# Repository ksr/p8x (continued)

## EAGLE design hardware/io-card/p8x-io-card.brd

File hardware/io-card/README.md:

# I/O Card

> **Theory of operation:** [p8x-io-card-theory.md](p8x-io-card-theory.md) — deep walkthrough of inputs/outputs, signal flow, and logic.

All memory-mapped I/O lives here: an 8-switch input port, an 8-LED output port,
**two** RS-232 serial channels via 6850 ACIAs (rev B), and a passive **bus-monitor**
LED display that turns the machine into an Altair-style "watch it think" front panel.

> **Rev B (2026-09-19)** — the routed KiCad board in [`kicad/`](kicad/README.md)
> (not yet fabricated) adds a second 6850 (**U17**, ACIA2 at `$FF08/09`, the
> Kermit / serial-terminal port) on the MAX232's second channel, with its E-gate
> inverter in **U18** (74HCT14). Each channel has its own **DB9** socket and a
> 2×3 jumper block that swaps RX/TX (straight or null-modem). A DS1302 real-time
> clock (**U16**) is provisioned but not fitted (DNP): it is a bit-banged 3-wire
> part on header J3, not memory-mapped. The text below describes the rev A
> circuit, which rev B keeps.

| Address | Port |
|---------|------|
| `$FF00` | Switch input — 8 toggle switches → data bus on read |
| `$FF02` | LED output — 74374 latch → 8 LEDs on write |
| `$FF04` | 6850 ACIA control/status |
| `$FF05` | 6850 ACIA data (RS-232 TX/RX) |
| `$FF08` | ACIA2 control/status (rev B) |
| `$FF09` | ACIA2 data (rev B) |

> This README describes the circuit as actually built in
> [`generators/gen_eagle.py`](../../generators/gen_eagle.py). See
> [p8x-system-design.md §7](../../docs/p8x-system-design.md) for the overview and
> [p8x-bus-definition.md](../backplane/p8x-bus-definition.md) for bus pins.

## Chip inventory

| Ref | Device | Role |
|-----|--------|------|
| U1 | 7430 | 8-input NAND — I/O page ($FFxx) detector |
| U2 | 74138 | Port decoder (A1–A3 → up to 8 port selects) |
| U3 | 74138 | DOE decoder (read enable) |
| U4 | 74138 | DLD decoder (write strobe) |
| U5 | 74HCT32 | OR glue (read/write strobe gating) |
| U6 | 74HCT08 | AND glue (ACIA enable) |
| U7 | 74161 | Baud-rate divider |
| U8 | MAX232 | RS-232 level shifter (the one non-TTL part) |
| U9 | 74244 | Switch-input buffer |
| U10 | 74374 | LED output latch |
| U11–U13 | 74244 | Bus monitors — A0–7, A8–15, D0–7 |
| U14 | 6850 | ACIA (asynchronous serial) |
| U15 | 74HCT00 | NAND glue |
| U16 | DS1302 | Real-time clock, DNP (rev B; 3-wire on J3, not memory-mapped) |
| U17 | 6850 | ACIA2 at `$FF08/09` (rev B) |
| U18 | 74HCT14 | Inverter — ACIA2 enable gate (rev B) |
| X2 | 2.4576 MHz osc | Baud clock source |

## How it works

### Port decoding
U1 (7430) detects the `$FFxx` page exactly as on the memory card. Within the page,
U2 (74138) decodes the low address lines into individual port selects (`-P0`, `-P1`,
`-P2`, …). Read vs write comes from the DOE decoder (U3 → `-RD`) and DLD decoder
(U4 → `-MEMW`), gated in U5/U6 into per-port read/write strobes.

### Switch input ($FF00)
Eight toggle switches with a SIP pull-up network feed a 74244 (U9). On a read of
`$FF00`, U9 is enabled and drives the switch states onto D0–D7.

### LED output ($FF02)
On a write to `$FF02`, the 74374 (U10) latches D0–D7. Its outputs drive an LED bank
through series-resistor networks, so the port value is visible at a glance.

### Serial (6850 ACIA, $FF04–$FF05)
The **6850 ACIA** (U14) handles asynchronous serial. Its enable is the `$FF04/05`
port select gated with the clock (U6/U15) for correct E-clock timing. A **74161**
(U7) divides the dedicated **2.4576 MHz** oscillator (X2) by 16 to make the
TX/RX baud clock. The **MAX232** (U8) — the one concession to non-TTL parts —
converts the ACIA's TTL levels to/from RS-232 ±voltages on the serial header,
using its four external charge-pump capacitors.

### Bus-monitor display (passive)
Three 74244 buffers (U11/U12/U13) permanently sample A0–7, A8–15, and D0–7 and
drive three LED banks. They cost nothing logically — no decode, no bus access —
but combined with the control card's single-step button they let you literally
watch the address and data buses change one microcycle at a time.

## Bus codes this card owns
- **DOE:** 7 = read (the active port drives D0–D7) — shared decode convention with memory
- **DLD:** 7 = write (`MEMW`) — the active port latches D0–D7

## LEDs
PWR (green), IOSEL (yellow — an I/O port is selected), plus the LED output port and
the 24-bit bus-monitor banks.

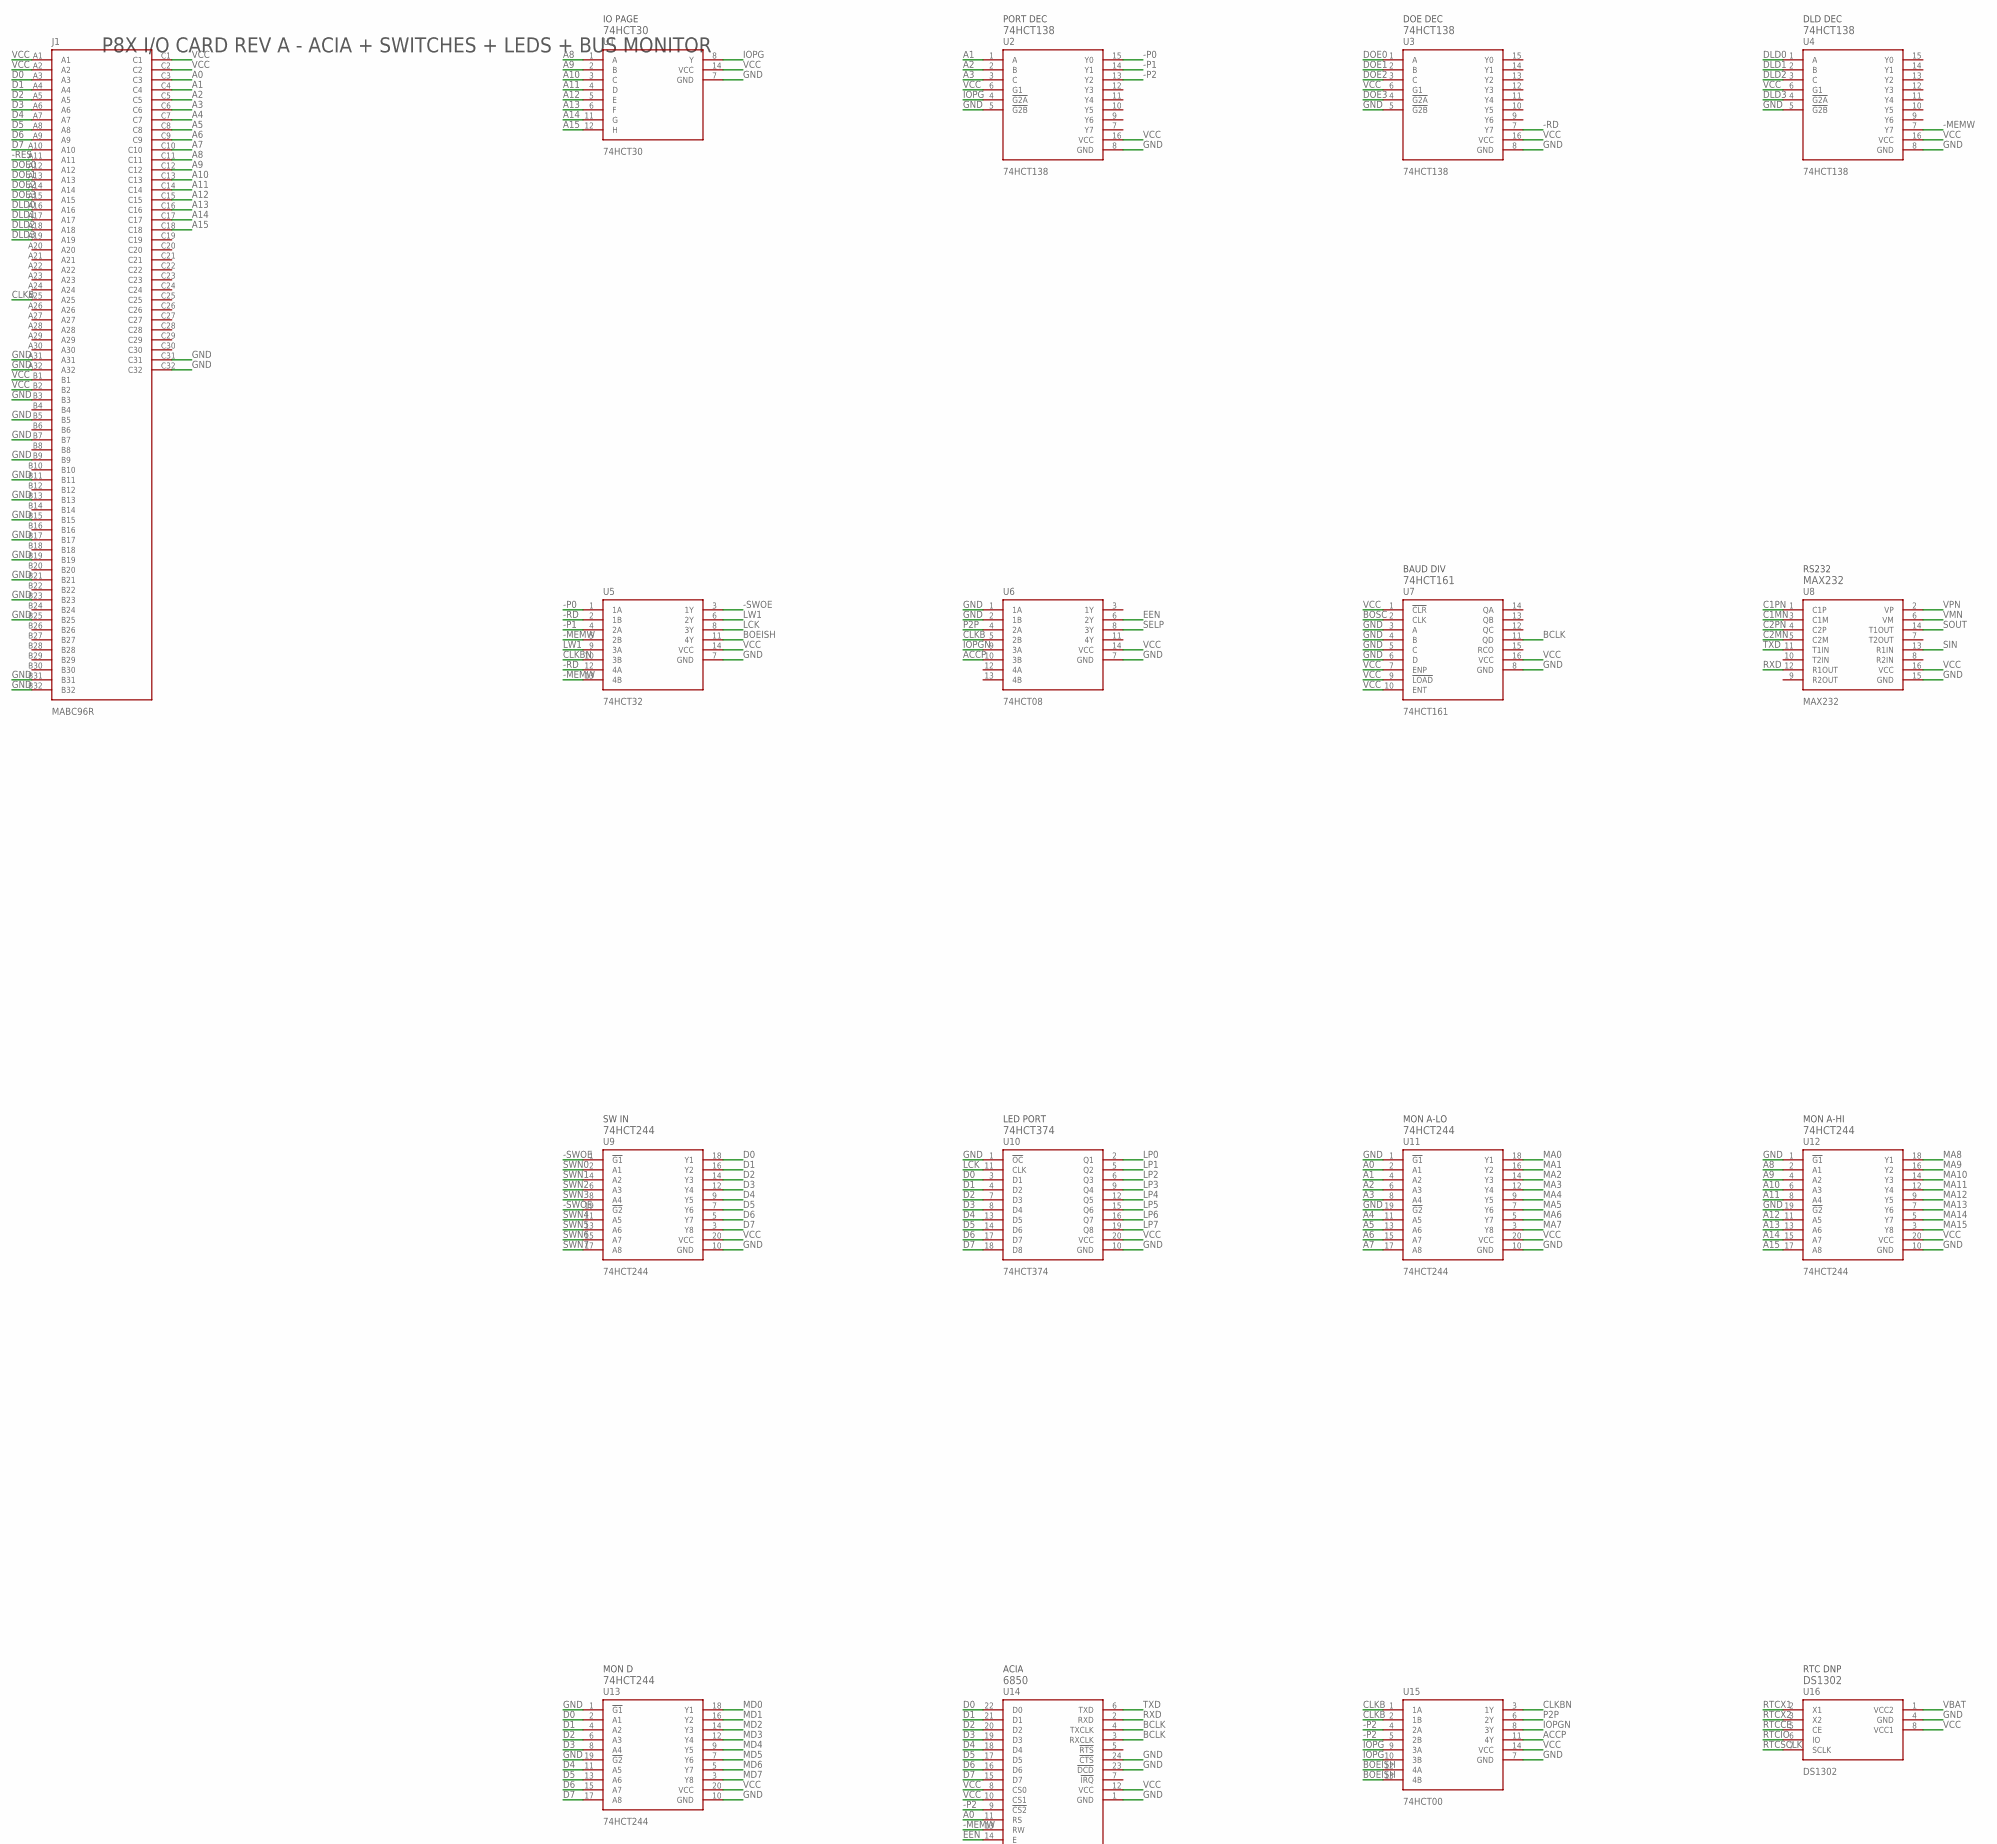
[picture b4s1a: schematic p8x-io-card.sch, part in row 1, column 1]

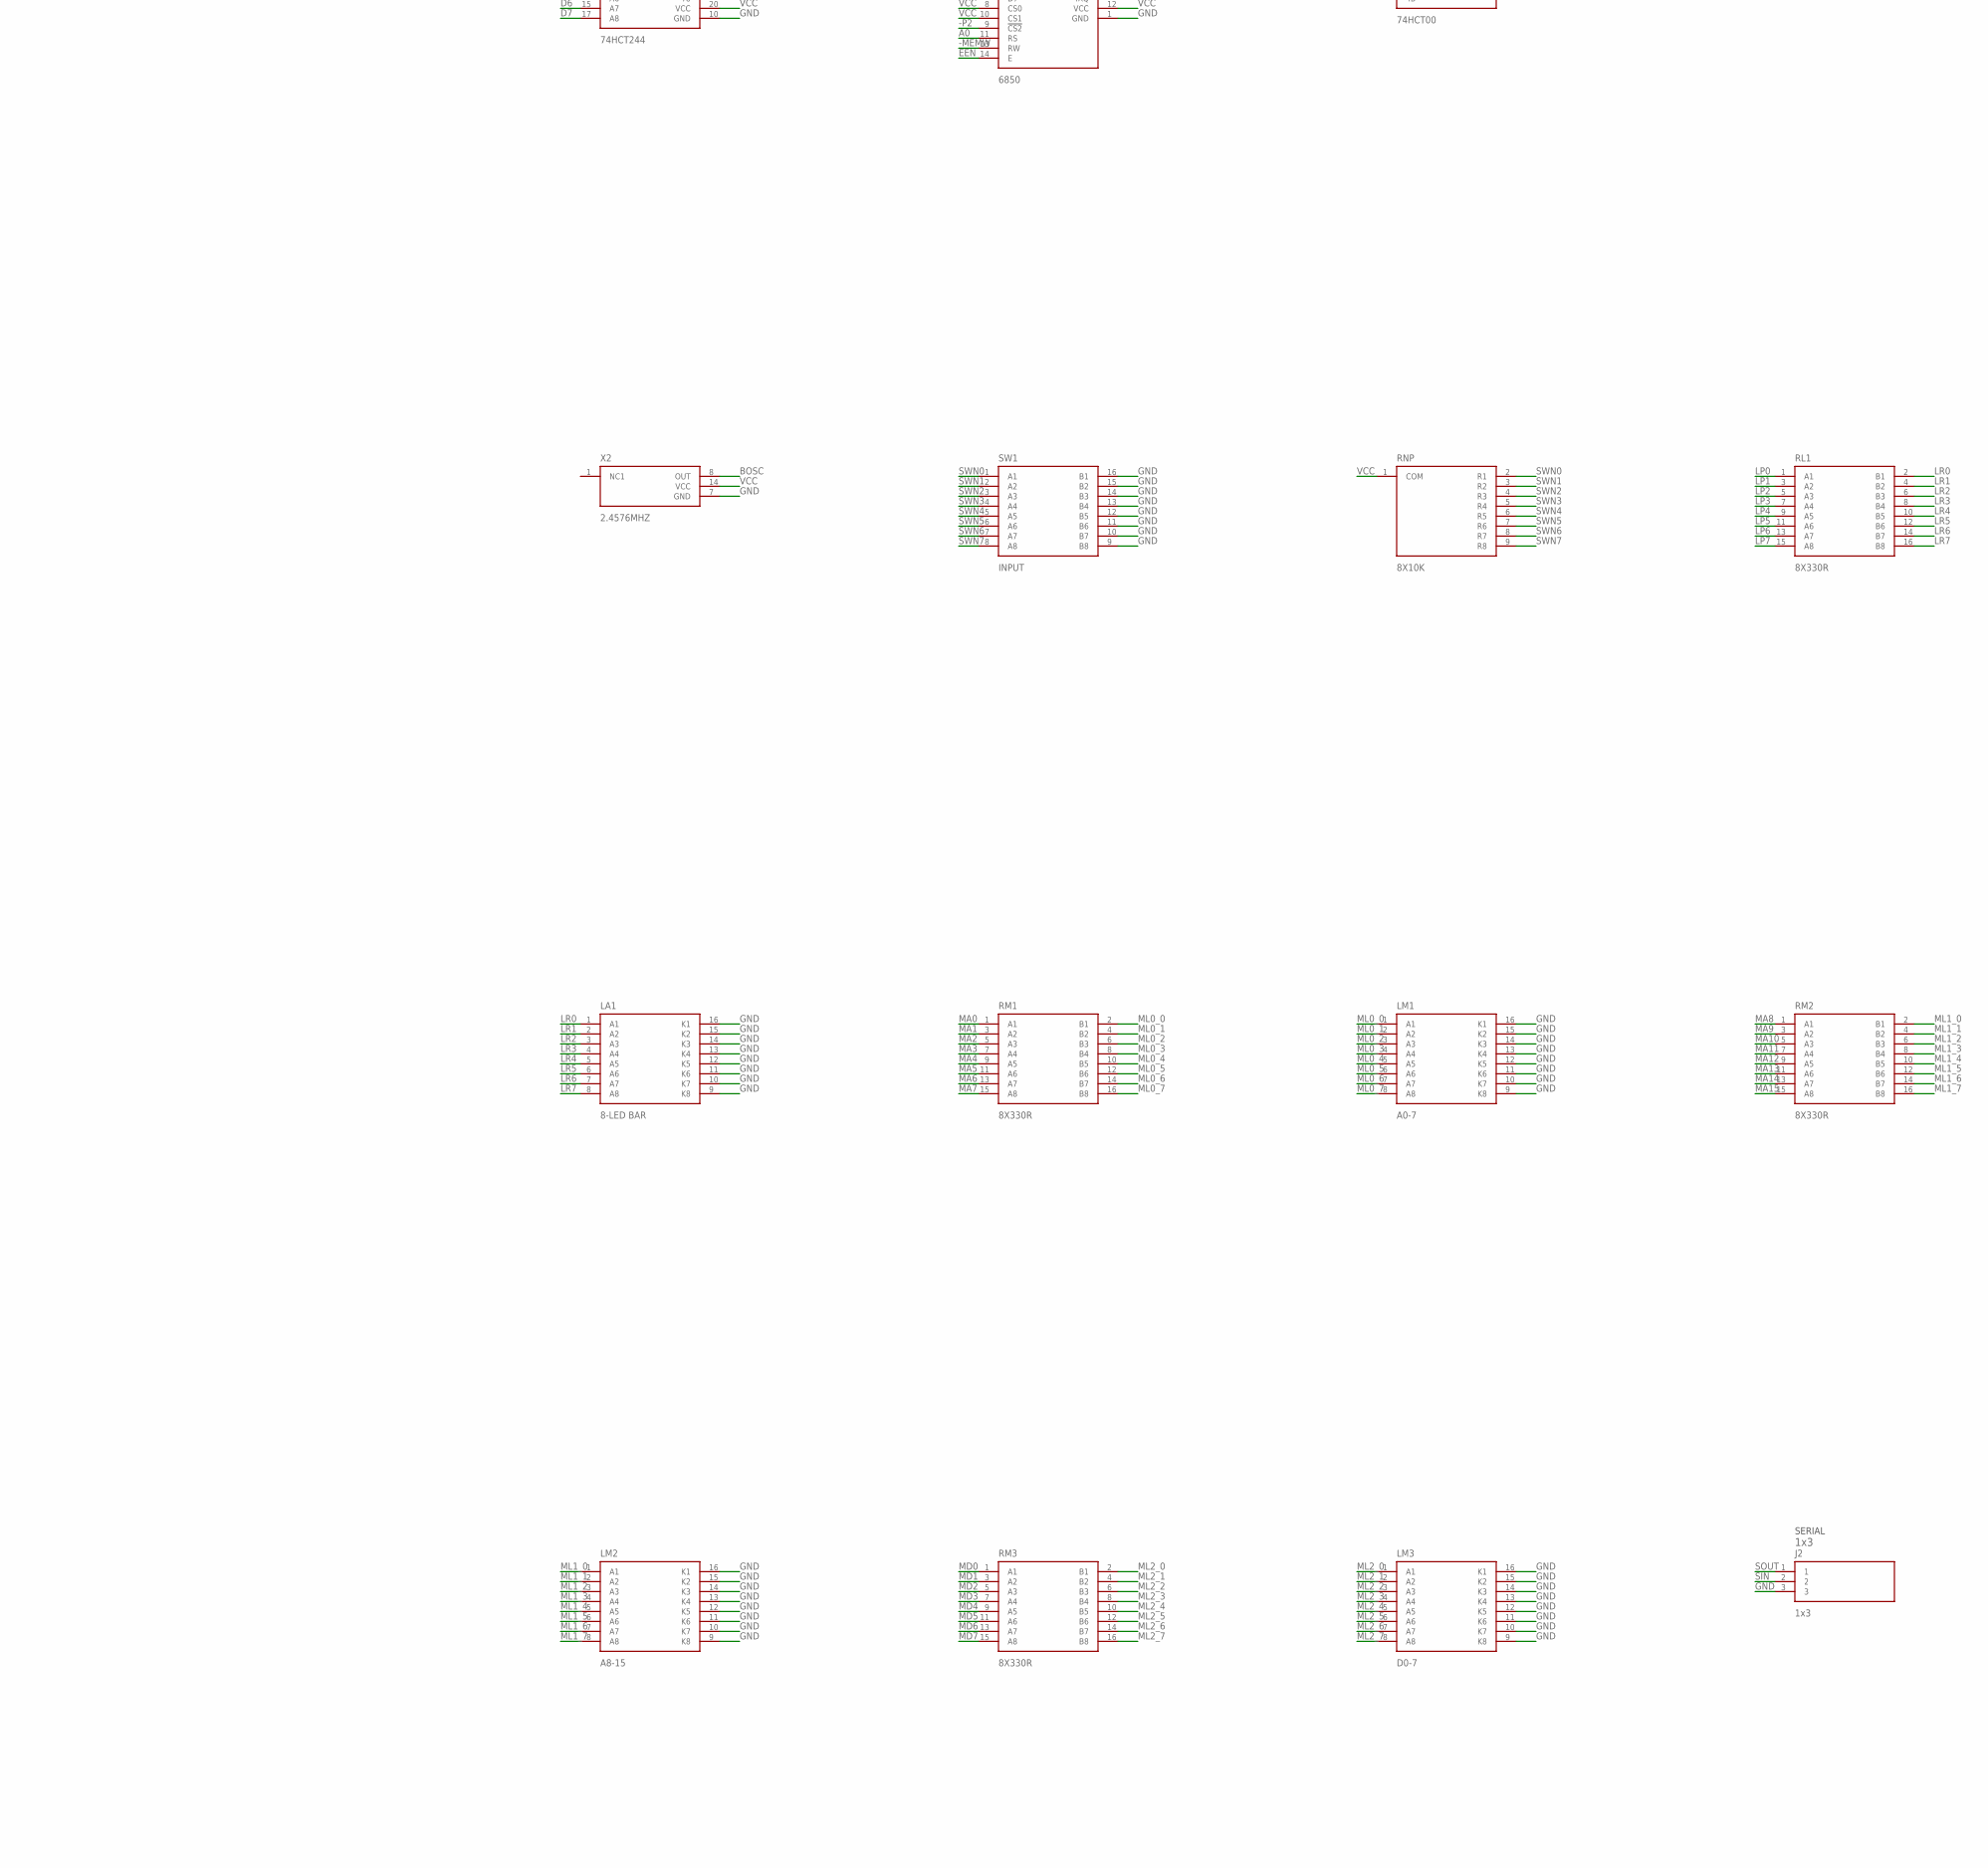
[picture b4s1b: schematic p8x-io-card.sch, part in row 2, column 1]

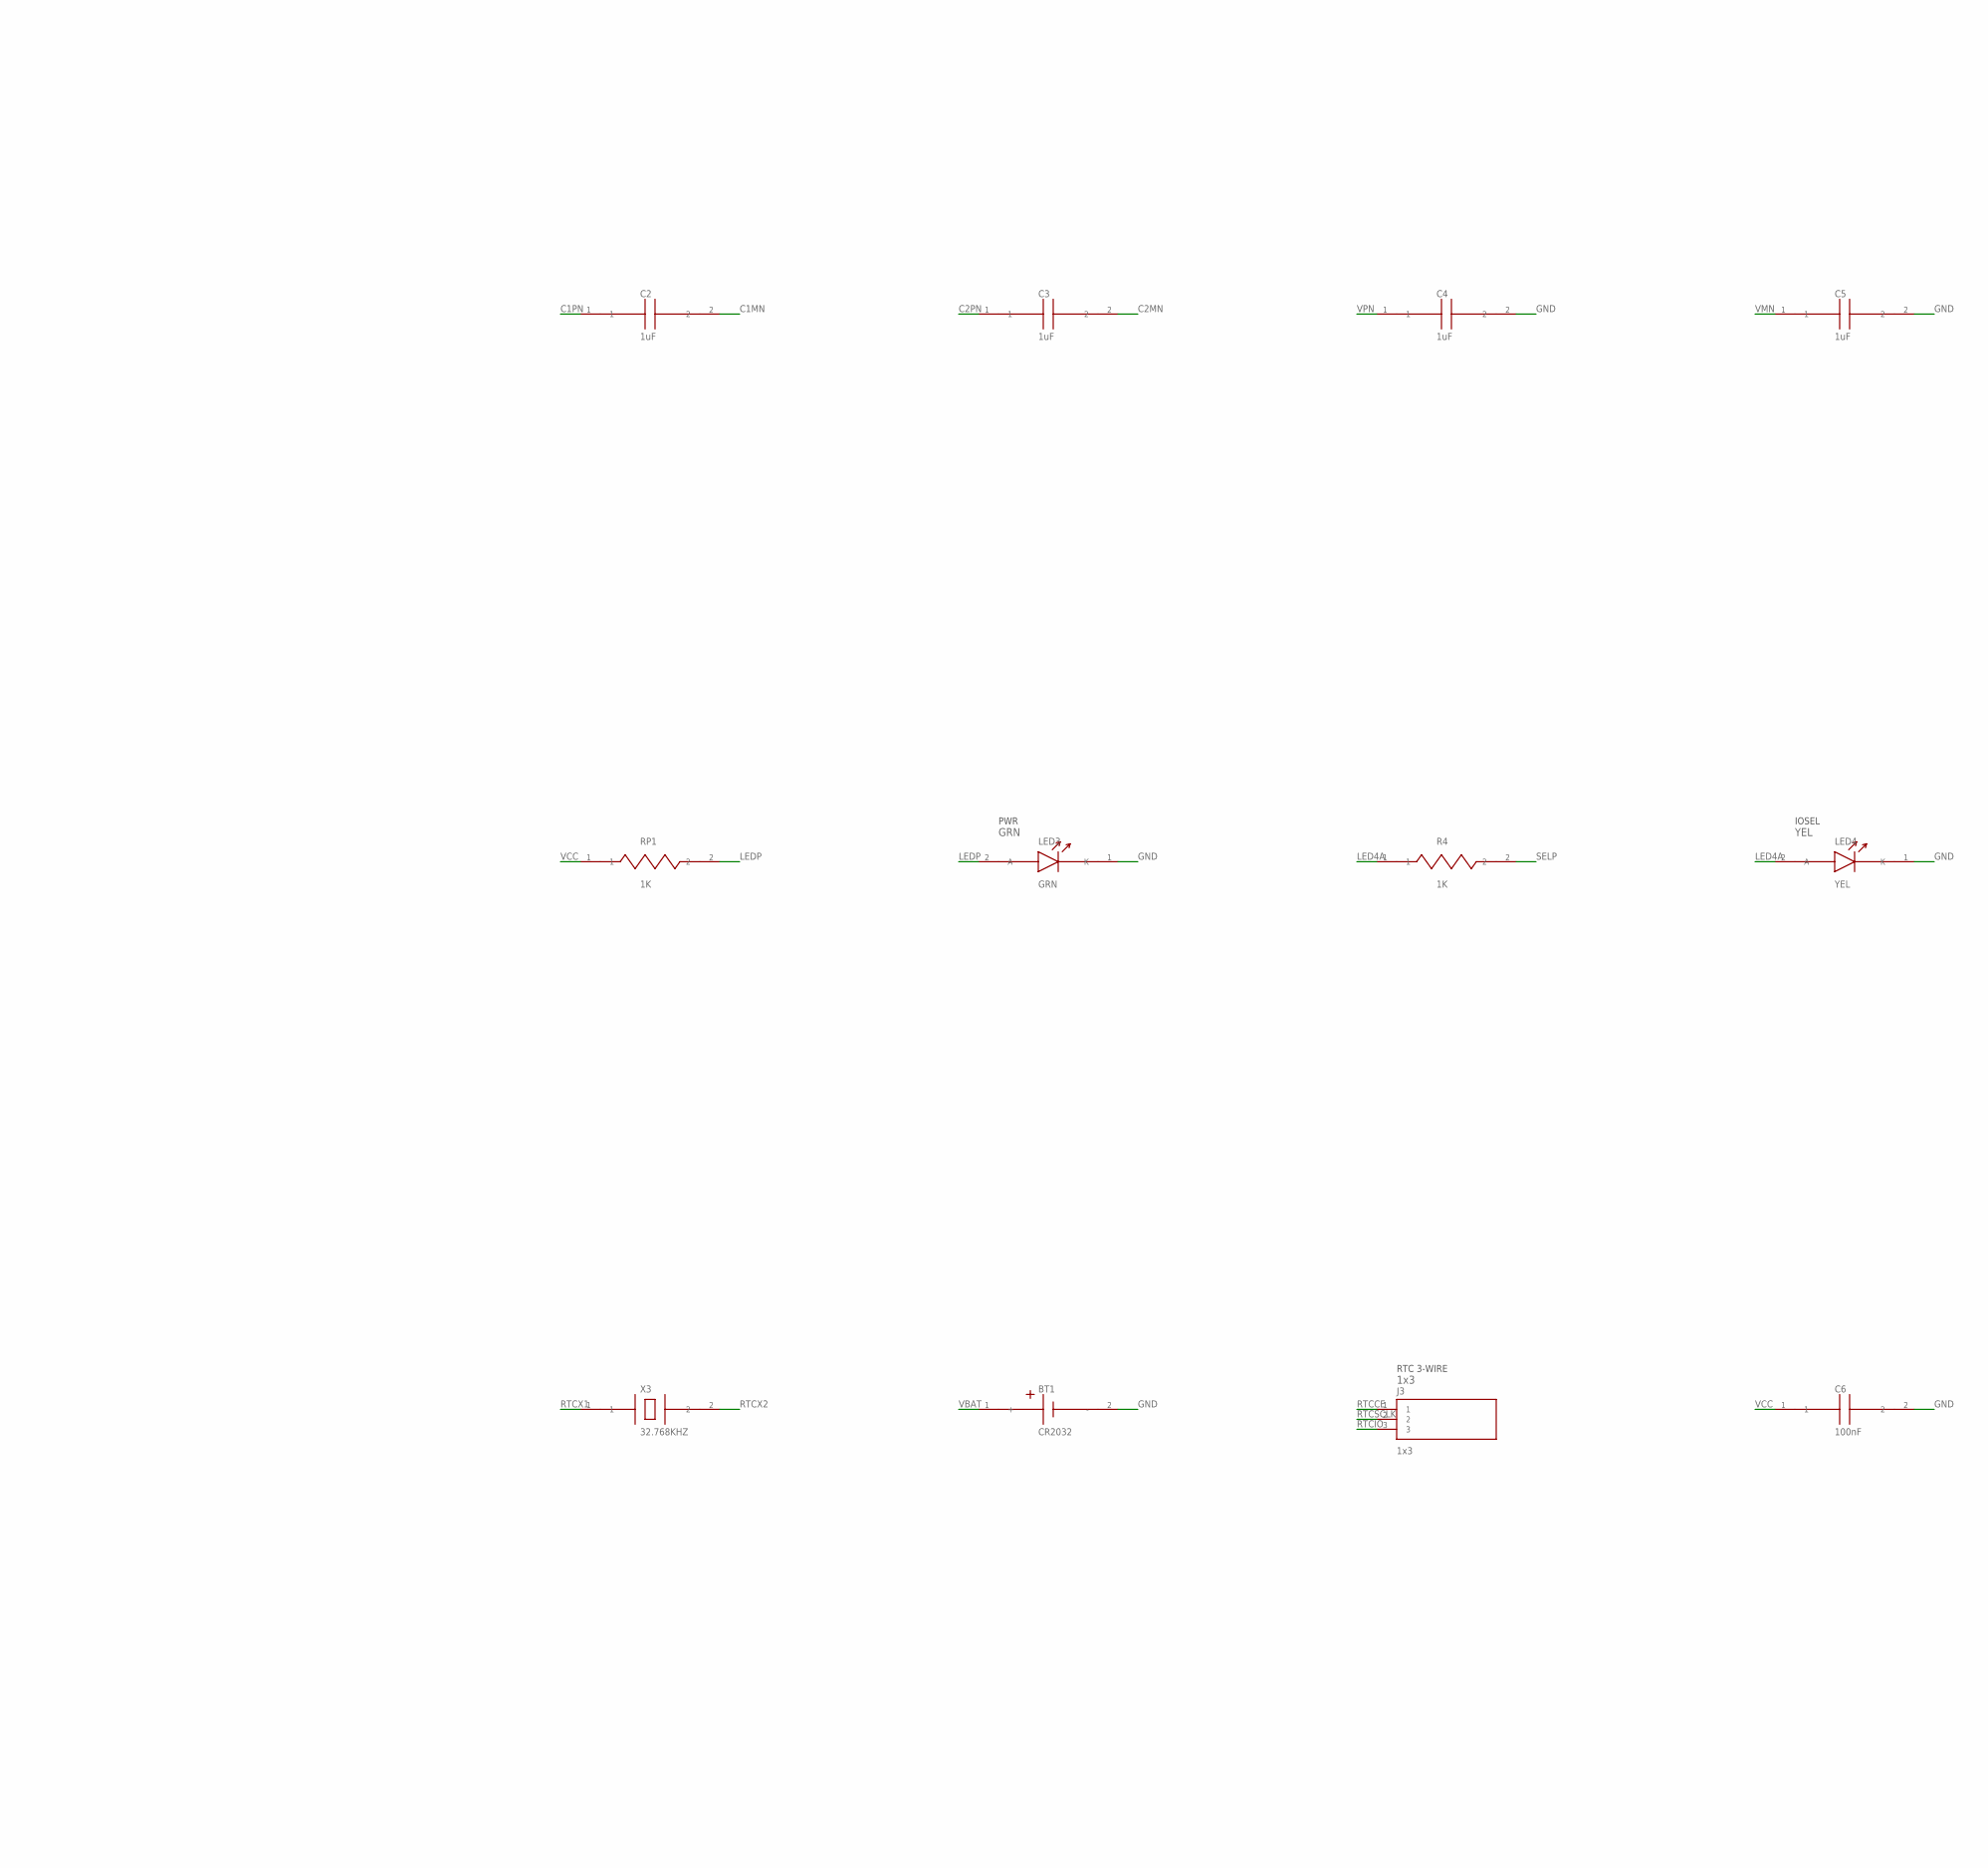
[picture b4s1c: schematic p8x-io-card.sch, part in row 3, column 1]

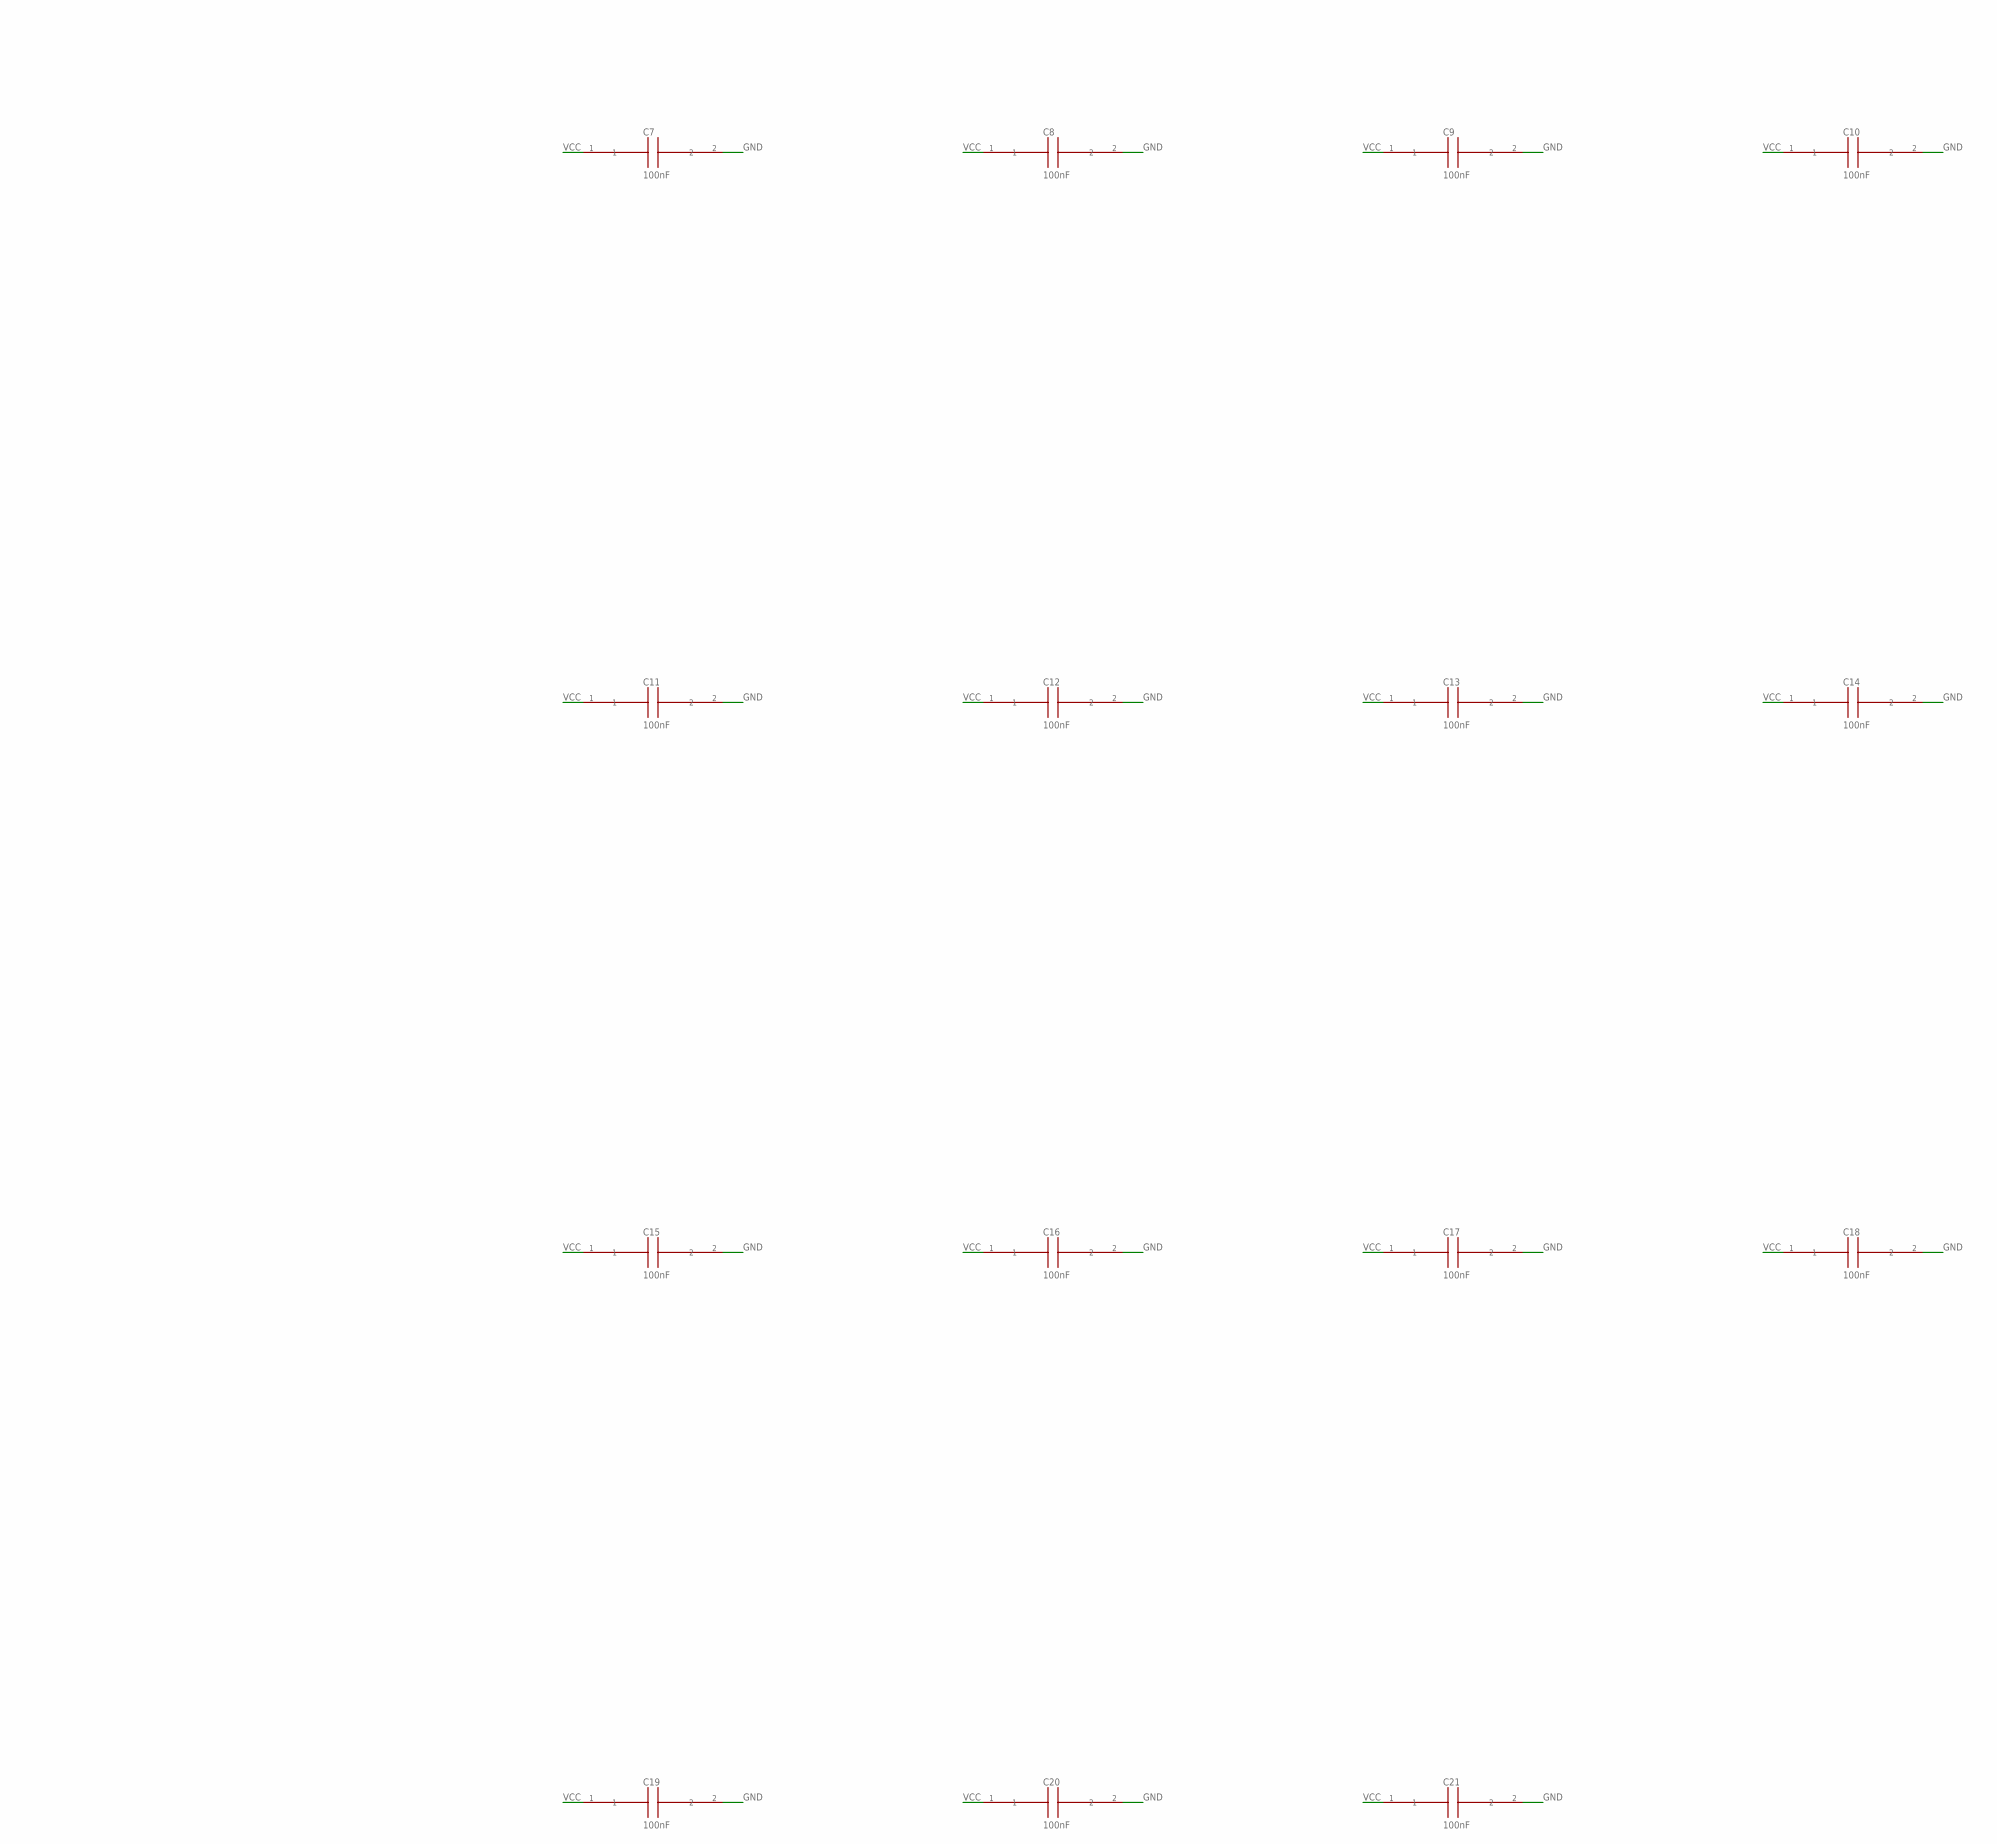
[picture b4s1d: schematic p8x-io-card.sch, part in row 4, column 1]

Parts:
BT1: CR2032; CP_RADIAL
C2, C3, C4, C5: 1uF; C_DISC
C6, C7, C8, C9, C10, C11, C12, C13, C14, C15, C16, C17, C18, C19, C20, C21: 100nF; C_DISC1
J1: MABC96R
J2, J3: 1x3; HDR3
LA1: 8-LED BAR; DIP16
LED3: GRN; LED5
LED4: YEL; LED5
LM1: A0-7; DIP16
LM2: A8-15; DIP16
LM3: D0-7; DIP16
R4: 1K; R_AXIAL
RL1: 8X330R; SIP16
RM1, RM2, RM3: 8X330R; SIP16
RNP: 8X10K; SIP9
RP1: 1K; R_AXIAL
SW1: INPUT; DIP16
U1: 74HCT30; DIP14
U2, U3, U4: 74HCT138; DIP16
U5: 74HCT32; DIP14
U6: 74HCT08; DIP14
U7: 74HCT161; DIP16
U8: MAX232; DIP16
U9, U11, U12, U13: 74HCT244; DIP20
U10: 74HCT374; DIP20
U14: 6850; DIP24W
U15: 74HCT00; DIP14
U16: DS1302; DIP8
X2: 2.4576MHZ; OSC4
X3: 32.768KHZ; C_DISC

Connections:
-MEMW: U4.7 (Y7), U5.5 (2B), U5.13 (4B), U14.13 (RW)
-P0: U2.15 (Y0), U5.1 (1A)
-P1: U2.14 (Y1), U5.4 (2A)
-P2: U2.13 (Y2), U14.9 (!CS2), U15.4 (2A), U15.5 (2B)
-RD: U3.7 (Y7), U5.2 (1B), U5.12 (4A)
-RES: J1.A11
-SWOE: U5.3 (1Y), U9.1 (!G1), U9.19 (!G2)
A0: J1.C3, U11.2 (A1), U14.11 (RS)
A1: J1.C4, U2.1 (A), U11.4 (A2)
A2: J1.C5, U2.2 (B), U11.6 (A3)
A3: J1.C6, U2.3 (C), U11.8 (A4)
A4: J1.C7, U11.11 (A5)
A5: J1.C8, U11.13 (A6)
A6: J1.C9, U11.15 (A7)
A7: J1.C10, U11.17 (A8)
A8: J1.C11, U1.1 (A), U12.2 (A1)
A9: J1.C12, U1.2 (B), U12.4 (A2)
A10: J1.C13, U1.3 (C), U12.6 (A3)
A11: J1.C14, U1.4 (D), U12.8 (A4)
A12: J1.C15, U1.5 (E), U12.11 (A5)
A13: J1.C16, U1.6 (F), U12.13 (A6)
A14: J1.C17, U1.11 (G), U12.15 (A7)
A15: J1.C18, U1.12 (H), U12.17 (A8)
ACCP: U6.10 (3B), U15.11 (4Y)
BCLK: U7.11 (QD), U14.3 (RXCLK), U14.4 (TXCLK)
BOEISH: U5.11 (4Y), U15.12 (4A), U15.13 (4B)
BOSC: U7.2 (CLK), X2.8 (OUT)
C1MN: C2.2, U8.3 (C1M)
C1PN: C2.1, U8.1 (C1P)
C2MN: C3.2, U8.5 (C2M)
C2PN: C3.1, U8.4 (C2P)
CLKB: J1.A25, U6.5 (2B), U15.1 (1A), U15.2 (1B)
CLKBN: U5.10 (3B), U15.3 (1Y)
D0: J1.A3, U9.18 (Y1), U10.3 (D1), U13.2 (A1), U14.22 (D0)
D1: J1.A4, U9.16 (Y2), U10.4 (D2), U13.4 (A2), U14.21 (D1)
D2: J1.A5, U9.14 (Y3), U10.7 (D3), U13.6 (A3), U14.20 (D2)
D3: J1.A6, U9.12 (Y4), U10.8 (D4), U13.8 (A4), U14.19 (D3)
D4: J1.A7, U9.9 (Y5), U10.13 (D5), U13.11 (A5), U14.18 (D4)
D5: J1.A8, U9.7 (Y6), U10.14 (D6), U13.13 (A6), U14.17 (D5)
D6: J1.A9, U9.5 (Y7), U10.17 (D7), U13.15 (A7), U14.16 (D6)
D7: J1.A10, U9.3 (Y8), U10.18 (D8), U13.17 (A8), U14.15 (D7)
DLD0: J1.A16, U4.1 (A)
DLD1: J1.A17, U4.2 (B)
DLD2: J1.A18, U4.3 (C)
DLD3: J1.A19, U4.4 (!G2A)
DOE0: J1.A12, U3.1 (A)
DOE1: J1.A13, U3.2 (B)
DOE2: J1.A14, U3.3 (C)
DOE3: J1.A15, U3.4 (!G2A)
EEN: U6.6 (2Y), U14.14 (E)
GND: BT1.2 (-), C4.2, C5.2, C6.2, C7.2, C8.2, C9.2, C10.2, C11.2, C12.2, C13.2, C14.2, C15.2, C16.2, C17.2, C18.2, C19.2, C20.2, C21.2, J1.A31, J1.A32, J1.B3, J1.B5, J1.B7, J1.B9, J1.B11, J1.B13, J1.B15, J1.B17, J1.B19, J1.B21, J1.B23, J1.B25, J1.B31, J1.B32, J1.C31, J1.C32, J2.3, LA1.9 (K8), LA1.10 (K7), LA1.11 (K6), LA1.12 (K5), LA1.13 (K4), LA1.14 (K3), LA1.15 (K2), LA1.16 (K1), LED3.1 (K), LED4.1 (K), LM1.9 (K8), LM1.10 (K7), LM1.11 (K6), LM1.12 (K5), LM1.13 (K4), LM1.14 (K3), LM1.15 (K2), LM1.16 (K1), LM2.9 (K8), LM2.10 (K7), LM2.11 (K6), LM2.12 (K5), LM2.13 (K4), LM2.14 (K3), LM2.15 (K2), LM2.16 (K1), LM3.9 (K8), LM3.10 (K7), LM3.11 (K6), LM3.12 (K5), LM3.13 (K4), LM3.14 (K3), LM3.15 (K2), LM3.16 (K1), SW1.9 (B8), SW1.10 (B7), SW1.11 (B6), SW1.12 (B5), SW1.13 (B4), SW1.14 (B3), SW1.15 (B2), SW1.16 (B1), U1.7 (GND), U2.5 (!G2B), U2.8 (GND), U3.5 (!G2B), U3.8 (GND), U4.5 (!G2B), U4.8 (GND), U5.7 (GND), U6.1 (1A), U6.2 (1B), U6.7 (GND), U7.3 (A), U7.4 (B), U7.5 (C), U7.6 (D), U7.8 (GND), U8.15 (GND), U9.10 (GND), U10.1 (!OC), U10.10 (GND), U11.1 (!G1), U11.10 (GND), U11.19 (!G2), U12.1 (!G1), U12.10 (GND), U12.19 (!G2), U13.1 (!G1), U13.10 (GND), U13.19 (!G2), U14.1 (GND), U14.23 (!DCD), U14.24 (!CTS), U15.7 (GND), U16.4 (GND), X2.7 (GND)
IOPG: U1.8 (Y), U2.4 (!G2A), U15.9 (3A), U15.10 (3B)
IOPGN: U6.9 (3A), U15.8 (3Y)
LCK: U5.8 (3Y), U10.11 (CLK)
LED4A: LED4.2 (A), R4.1
LEDP: LED3.2 (A), RP1.2
LP0: RL1.1 (A1), U10.2 (Q1)
LP1: RL1.3 (A2), U10.5 (Q2)
LP2: RL1.5 (A3), U10.6 (Q3)
LP3: RL1.7 (A4), U10.9 (Q4)
LP4: RL1.9 (A5), U10.12 (Q5)
LP5: RL1.11 (A6), U10.15 (Q6)
LP6: RL1.13 (A7), U10.16 (Q7)
LP7: RL1.15 (A8), U10.19 (Q8)
LR0: LA1.1 (A1), RL1.2 (B1)
LR1: LA1.2 (A2), RL1.4 (B2)
LR2: LA1.3 (A3), RL1.6 (B3)
LR3: LA1.4 (A4), RL1.8 (B4)
LR4: LA1.5 (A5), RL1.10 (B5)
LR5: LA1.6 (A6), RL1.12 (B6)
LR6: LA1.7 (A7), RL1.14 (B7)
LR7: LA1.8 (A8), RL1.16 (B8)
LW1: U5.6 (2Y), U5.9 (3A)
MA0: RM1.1 (A1), U11.18 (Y1)
MA1: RM1.3 (A2), U11.16 (Y2)
MA2: RM1.5 (A3), U11.14 (Y3)
MA3: RM1.7 (A4), U11.12 (Y4)
MA4: RM1.9 (A5), U11.9 (Y5)
MA5: RM1.11 (A6), U11.7 (Y6)
MA6: RM1.13 (A7), U11.5 (Y7)
MA7: RM1.15 (A8), U11.3 (Y8)
MA8: RM2.1 (A1), U12.18 (Y1)
MA9: RM2.3 (A2), U12.16 (Y2)
MA10: RM2.5 (A3), U12.14 (Y3)
MA11: RM2.7 (A4), U12.12 (Y4)
MA12: RM2.9 (A5), U12.9 (Y5)
MA13: RM2.11 (A6), U12.7 (Y6)
MA14: RM2.13 (A7), U12.5 (Y7)
MA15: RM2.15 (A8), U12.3 (Y8)
MD0: RM3.1 (A1), U13.18 (Y1)
MD1: RM3.3 (A2), U13.16 (Y2)
MD2: RM3.5 (A3), U13.14 (Y3)
MD3: RM3.7 (A4), U13.12 (Y4)
MD4: RM3.9 (A5), U13.9 (Y5)
MD5: RM3.11 (A6), U13.7 (Y6)
MD6: RM3.13 (A7), U13.5 (Y7)
MD7: RM3.15 (A8), U13.3 (Y8)
ML0_0: LM1.1 (A1), RM1.2 (B1)
ML0_1: LM1.2 (A2), RM1.4 (B2)
ML0_2: LM1.3 (A3), RM1.6 (B3)
ML0_3: LM1.4 (A4), RM1.8 (B4)
ML0_4: LM1.5 (A5), RM1.10 (B5)
ML0_5: LM1.6 (A6), RM1.12 (B6)
ML0_6: LM1.7 (A7), RM1.14 (B7)
ML0_7: LM1.8 (A8), RM1.16 (B8)
ML1_0: LM2.1 (A1), RM2.2 (B1)
ML1_1: LM2.2 (A2), RM2.4 (B2)
ML1_2: LM2.3 (A3), RM2.6 (B3)
ML1_3: LM2.4 (A4), RM2.8 (B4)
ML1_4: LM2.5 (A5), RM2.10 (B5)
ML1_5: LM2.6 (A6), RM2.12 (B6)
ML1_6: LM2.7 (A7), RM2.14 (B7)
ML1_7: LM2.8 (A8), RM2.16 (B8)
ML2_0: LM3.1 (A1), RM3.2 (B1)
ML2_1: LM3.2 (A2), RM3.4 (B2)
ML2_2: LM3.3 (A3), RM3.6 (B3)
ML2_3: LM3.4 (A4), RM3.8 (B4)
ML2_4: LM3.5 (A5), RM3.10 (B5)
ML2_5: LM3.6 (A6), RM3.12 (B6)
ML2_6: LM3.7 (A7), RM3.14 (B7)
ML2_7: LM3.8 (A8), RM3.16 (B8)
P2P: U6.4 (2A), U15.6 (2Y)
RTCCE: J3.1, U16.5 (CE)
RTCIO: J3.3, U16.6 (IO)
RTCSCLK: J3.2, U16.7 (SCLK)
RTCX1: U16.2 (X1), X3.1
RTCX2: U16.3 (X2), X3.2
RXD: U8.12 (R1OUT), U14.2 (RXD)
SELP: R4.2, U6.8 (3Y)
SIN: J2.2, U8.13 (R1IN)
SOUT: J2.1, U8.14 (T1OUT)
SWN0: RNP.2 (R1), SW1.1 (A1), U9.2 (A1)
SWN1: RNP.3 (R2), SW1.2 (A2), U9.4 (A2)
SWN2: RNP.4 (R3), SW1.3 (A3), U9.6 (A3)
SWN3: RNP.5 (R4), SW1.4 (A4), U9.8 (A4)
SWN4: RNP.6 (R5), SW1.5 (A5), U9.11 (A5)
SWN5: RNP.7 (R6), SW1.6 (A6), U9.13 (A6)
SWN6: RNP.8 (R7), SW1.7 (A7), U9.15 (A7)
SWN7: RNP.9 (R8), SW1.8 (A8), U9.17 (A8)
TXD: U8.11 (T1IN), U14.6 (TXD)
VBAT: BT1.1 (+), U16.1 (VCC2)
VCC: C6.1, C7.1, C8.1, C9.1, C10.1, C11.1, C12.1, C13.1, C14.1, C15.1, C16.1, C17.1, C18.1, C19.1, C20.1, C21.1, J1.A1, J1.A2, J1.B1, J1.B2, J1.C1, J1.C2, RNP.1 (COM), RP1.1, U1.14 (VCC), U2.6 (G1), U2.16 (VCC), U3.6 (G1), U3.16 (VCC), U4.6 (G1), U4.16 (VCC), U5.14 (VCC), U6.14 (VCC), U7.1 (!CLR), U7.7 (ENP), U7.9 (!LOAD), U7.10 (ENT), U7.16 (VCC), U8.16 (VCC), U9.20 (VCC), U10.20 (VCC), U11.20 (VCC), U12.20 (VCC), U13.20 (VCC), U14.8 (CS0), U14.10 (CS1), U14.12 (VCC), U15.14 (VCC), U16.8 (VCC1), X2.14 (VCC)
VMN: C5.1, U8.6 (VM)
VPN: C4.1, U8.2 (VP)

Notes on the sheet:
P8X I/O CARD REV A - ACIA + SWITCHES + LEDS + BUS MONITOR
IO PAGE
74HCT30
PORT DEC
74HCT138
DOE DEC
DLD DEC
BAUD DIV
74HCT161
RS232
MAX232
SW IN
74HCT244
LED PORT
74HCT374
MON A-LO
MON A-HI
MON D
ACIA
6850
RTC DNP
DS1302
SERIAL
1x3
PWR
GRN
IOSEL
YEL
RTC 3-WIRE

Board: 4 copper layers, 56 parts (0 on the bottom side), 143 nets, no tracks yet.
